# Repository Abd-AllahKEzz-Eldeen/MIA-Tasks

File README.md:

# MIA-Tasks

https://www.tinkercad.com/things/jqynoGWIMv9-irrigation-system

https://www.tinkercad.com/things/fajDuiIjbEZ-smart-green-house

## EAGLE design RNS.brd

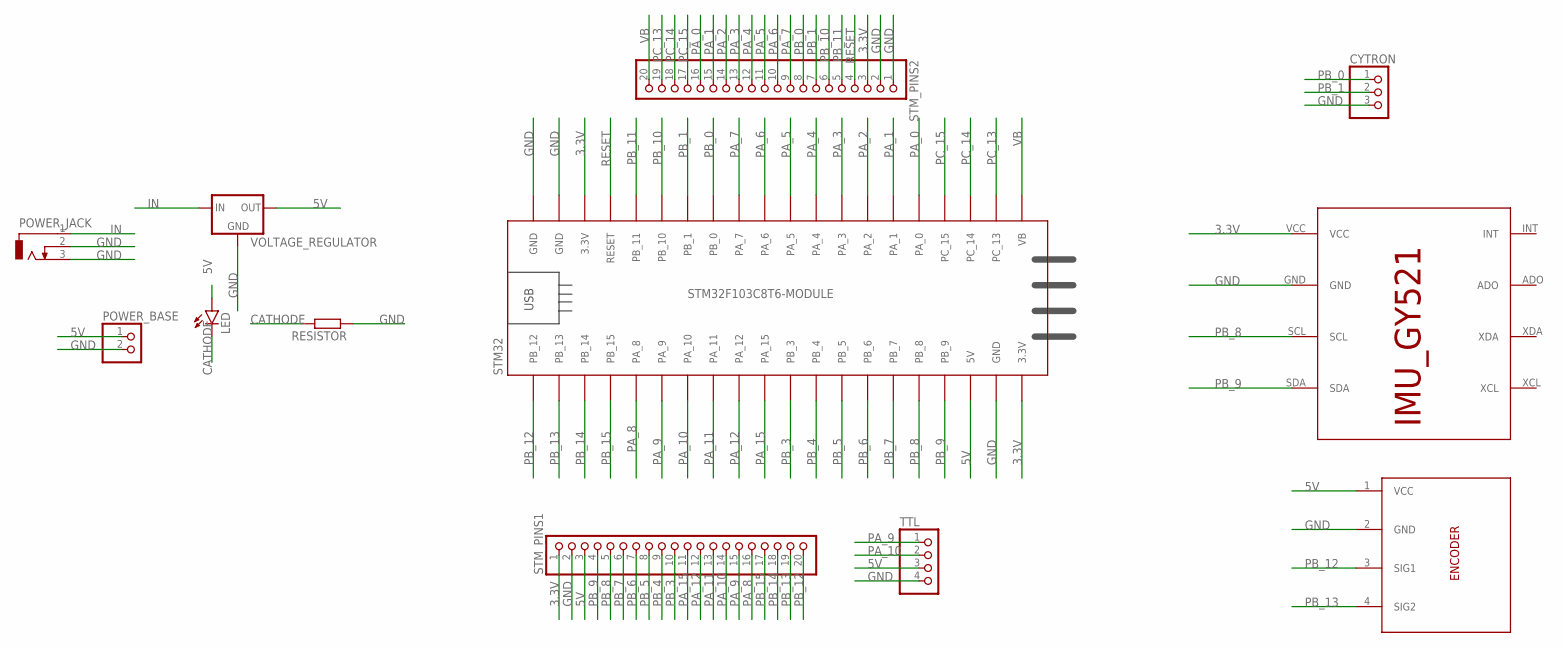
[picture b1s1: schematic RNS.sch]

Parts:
CYTRON: PINHD-3_DATA; 1X03_DATA
ENCODER: ENCODER; 1X04_DATA
IMU: IMU_ROBOCON_GY521; IMU_GY521
LED: LED5MM
POWER_BASE: PINHD-2_DATA; 1X02_DATA
POWER_JACK: CON_JACK; DCJ0303
RESISTOR: R-EU_0207/12; 0207/12
STM32: STM32F103C8T6-MODULE
STM_PINS1, STM_PINS2: PINHD-1X20; 1X20
TTL: PINHD-1X4; 1X04
VOLTAGE_REGULATOR: 78XXS

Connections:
3.3V: IMU.VCC, STM32.3.3V_1 (3.3V), STM32.3.3V_2 (3.3V), STM_PINS1.1, STM_PINS2.3
5V: ENCODER.1 (VCC), LED.A, POWER_BASE.1, STM32.5V, STM_PINS1.3, TTL.3, VOLTAGE_REGULATOR.OUT
CATHODE: LED.K (C), RESISTOR.2
GND: CYTRON.3, ENCODER.2 (GND), IMU.GND, POWER_BASE.2, POWER_JACK.2, POWER_JACK.3, RESISTOR.1, STM32.GND_1 (GND), STM32.GND_2 (GND), STM32.GND_3 (GND), STM_PINS1.2, STM_PINS2.1, STM_PINS2.2, TTL.4, VOLTAGE_REGULATOR.GND
IN: POWER_JACK.1, VOLTAGE_REGULATOR.IN
PA_0: STM32.PA_0, STM_PINS2.16
PA_1: STM32.PA_1, STM_PINS2.15
PA_2: STM32.PA_2, STM_PINS2.14
PA_3: STM32.PA_3, STM_PINS2.13
PA_4: STM32.PA_4, STM_PINS2.12
PA_5: STM32.PA_5, STM_PINS2.11
PA_6: STM32.PA_6, STM_PINS2.10
PA_7: STM32.PA_7, STM_PINS2.9
PA_8: STM32.PA_8, STM_PINS1.16
PA_9: STM32.PA_9, STM_PINS1.15, TTL.1
PA_10: STM32.PA_10, STM_PINS1.14, TTL.2
PA_11: STM32.PA_11, STM_PINS1.13
PA_12: STM32.PA_12, STM_PINS1.12
PA_15: STM32.PA_15, STM_PINS1.11
PB_0: CYTRON.1, STM32.PB_0, STM_PINS2.8
PB_1: CYTRON.2, STM32.PB_1, STM_PINS2.7
PB_3: STM32.PB_3, STM_PINS1.10
PB_4: STM32.PB_4, STM_PINS1.9
PB_5: STM32.PB_5, STM_PINS1.8
PB_6: STM32.PB_6, STM_PINS1.7
PB_7: STM32.PB_7, STM_PINS1.6
PB_8: IMU.SCL, STM32.PB_8, STM_PINS1.5
PB_9: IMU.SDA, STM32.PB_9, STM_PINS1.4
PB_10: STM32.PB_10, STM_PINS2.6
PB_11: STM32.PB_11, STM_PINS2.5
PB_12: ENCODER.3 (SIG1), STM32.PB_12, STM_PINS1.20
PB_13: ENCODER.4 (SIG2), STM32.PB_13, STM_PINS1.19
PB_14: STM32.PB_14, STM_PINS1.18
PB_15: STM32.PB_15, STM_PINS1.17
PC_13: STM32.PC_13, STM_PINS2.19
PC_14: STM32.PC_14, STM_PINS2.18
PC_15: STM32.PC_15, STM_PINS2.17
RESET: STM32.RESET, STM_PINS2.4
VB: STM32.VB, STM_PINS2.20

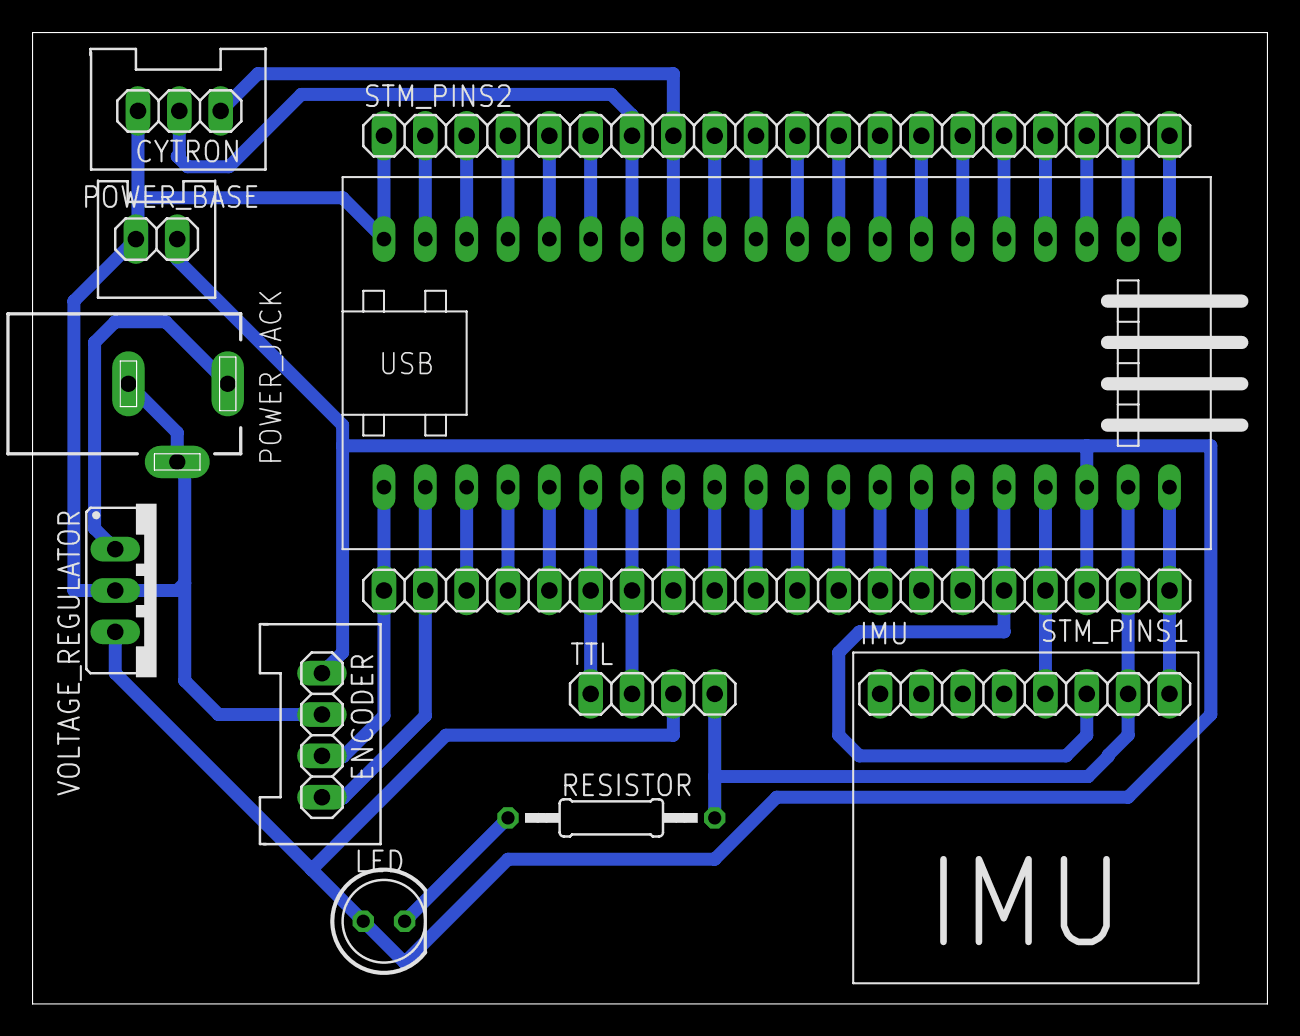
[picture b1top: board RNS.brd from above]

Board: 2 copper layers, 75.9 x 59.7 mm, 12 parts (0 on the bottom side), 39 nets.

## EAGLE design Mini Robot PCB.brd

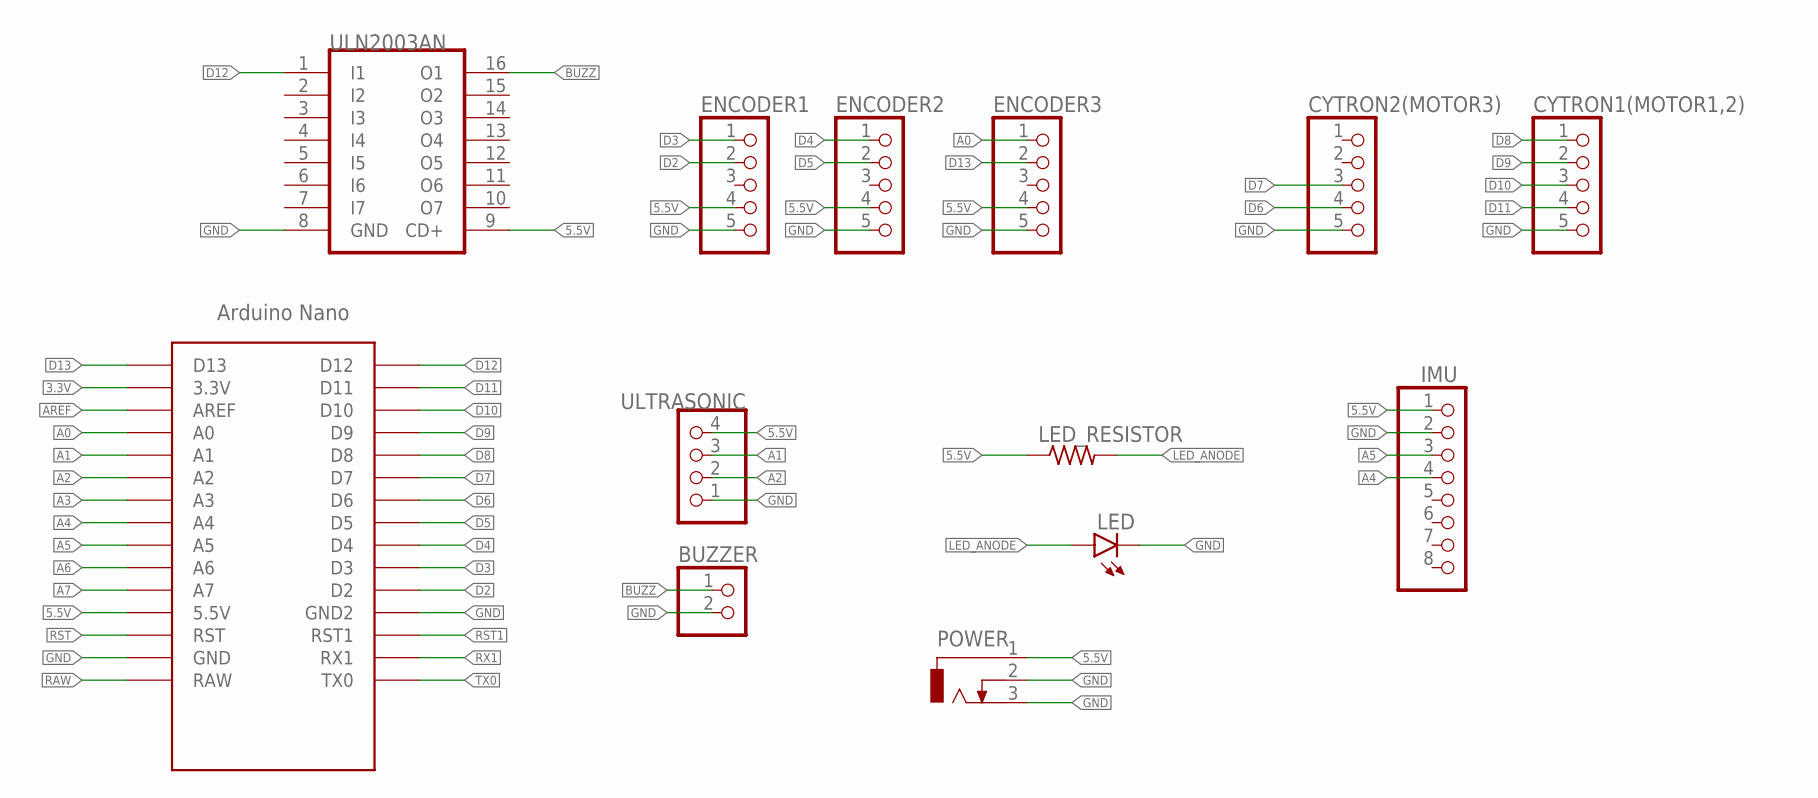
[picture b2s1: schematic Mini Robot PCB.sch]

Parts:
BUZZER: PINHD-1X2; 1X02
CYTRON1(MOTOR1,2), CYTRON2(MOTOR3): PINHD-1X5; 1X05
ENCODER1, ENCODER2, ENCODER3: PINHD-1X5; 1X05
IC1: ULN2003AN; DIL16
IMU: PINHD-1X8; 1X08
LED: LED5MM
LED_RESISTOR: RES-10; 0207/10
POWER: CON_JACK; DCJ0303
U$1: ARDUINO_NANO; NANO
ULTRASONIC: PINHD-1X4; 1X04

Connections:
3.3V: U$1.3.3V
5.5V: ENCODER1.4, ENCODER2.4, ENCODER3.4, IC1.9 (CD+), IMU.1, LED_RESISTOR.1, POWER.1, U$1.5V (5.5V), ULTRASONIC.4
A0: ENCODER3.1, U$1.A0
A1: U$1.A1, ULTRASONIC.3
A2: U$1.A2, ULTRASONIC.2
A3: U$1.A3
A4: IMU.4, U$1.A4
A5: IMU.3, U$1.A5
A6: U$1.A6
A7: U$1.A7
AREF: U$1.AREF
BUZZ: BUZZER.1, IC1.16 (O1)
D2: ENCODER1.2, U$1.D2
D3: ENCODER1.1, U$1.D3
D4: ENCODER2.1, U$1.D4
D5: ENCODER2.2, U$1.D5
D6: CYTRON2(MOTOR3).4, U$1.D6
D7: CYTRON2(MOTOR3).3, U$1.D7
D8: CYTRON1(MOTOR1,2).1, U$1.D8
D9: CYTRON1(MOTOR1,2).2, U$1.D9
D10: CYTRON1(MOTOR1,2).3, U$1.D10
D11: CYTRON1(MOTOR1,2).4, U$1.D11
D12: IC1.1 (I1), U$1.D12
D13: ENCODER3.2, U$1.D13
GND: BUZZER.2, CYTRON1(MOTOR1,2).5, CYTRON2(MOTOR3).5, ENCODER1.5, ENCODER2.5, ENCODER3.5, IC1.8 (GND), IMU.2, LED.K (C), POWER.2, POWER.3, U$1.GND, U$1.GND1 (GND2), ULTRASONIC.1
LED_ANODE: LED.A, LED_RESISTOR.2
RAW: U$1.RAW
RST: U$1.RST
RST1: U$1.RST1
RX1: U$1.RX1
TX0: U$1.TX0

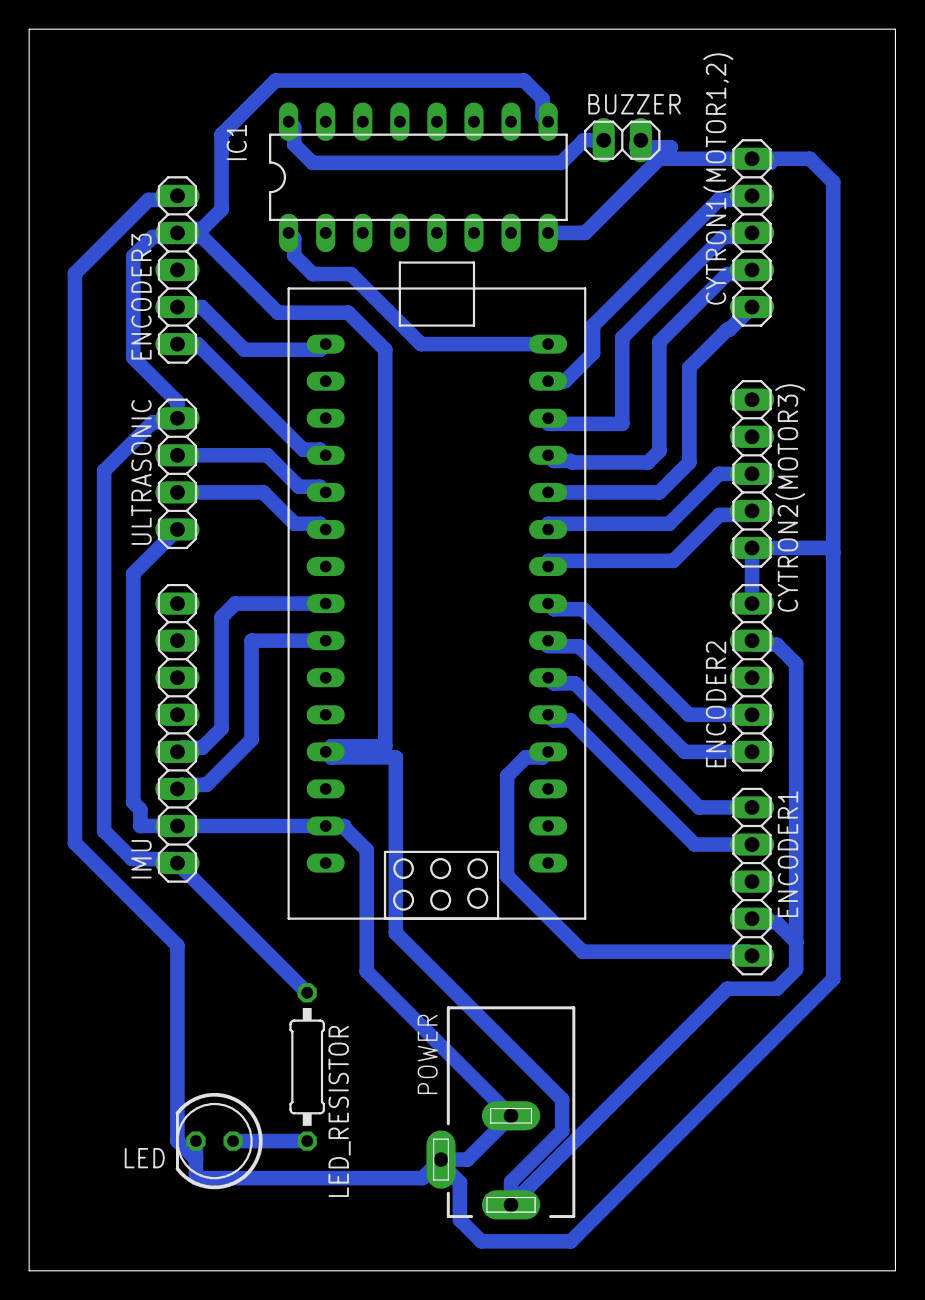
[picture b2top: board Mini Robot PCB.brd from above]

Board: 2 copper layers, 59.4 x 85.1 mm, 13 parts (0 on the bottom side), 21 nets.

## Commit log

2022-08-11 Add files via upload
    https://www.tinkercad.com/things/jqynoGWIMv9-irrigation-system
    https://www.tinkercad.com/things/fajDuiIjbEZ-smart-green-house
2022-08-22 Add files via upload
    Level18 = ByeBye!
